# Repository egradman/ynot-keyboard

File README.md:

# zmq-corne6

This is the repo for my "ynot" keyboard.

it uses:

- Panasonic EVQWGD001 (purchased from keebd, but you can find them on aliexpress)
- nicenano
- a r61 trackpoint harvested from this keyboard https://www.ebay.com/itm/255174965511.  see https://deskthority.net/wiki/TrackPoint_Hardware for the pinout.
- choc kailh whites
- custom laser cut case
- battery:  3.7v 110mAh 301230 see (https://typeractive.xyz/products/lithium-battery-110mah)

trackpoint reset circuit as described here https://github.com/alonswartz/trackpoint

and the firmware provided by infusedkim https://github.com/infused-kim/kb_zmk_ps2_mouse_trackpoint_driver

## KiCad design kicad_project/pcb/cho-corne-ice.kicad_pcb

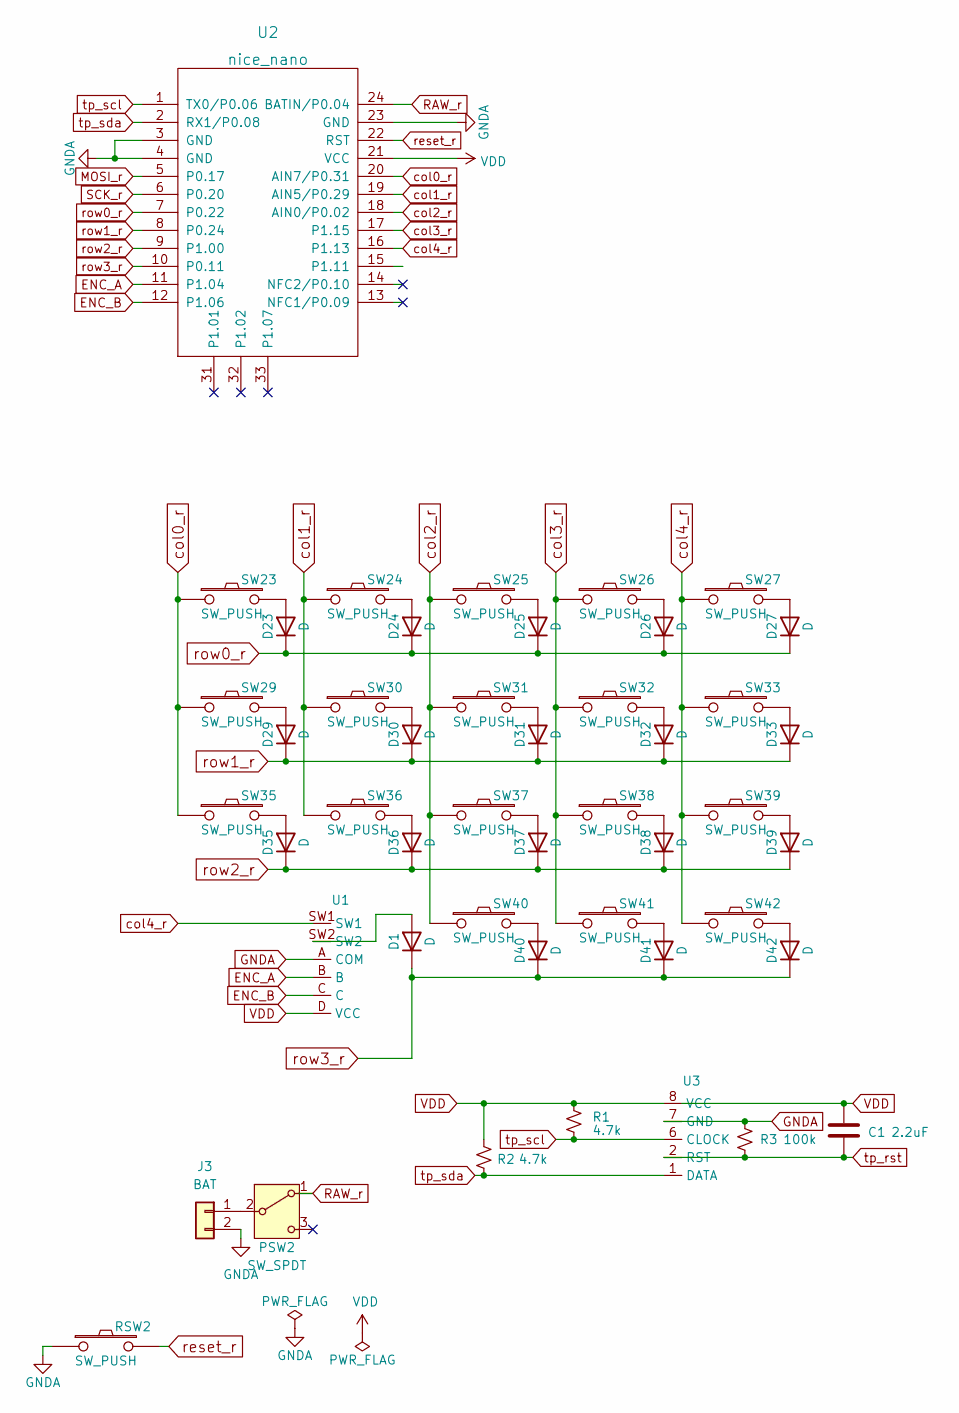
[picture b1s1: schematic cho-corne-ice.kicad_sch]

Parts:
C1: 2.2uF; CP_Radial_D4.0mm_P1.50mm
D1, D23, D24, D25, D26, D27, D29, D30, D31, D32, D33, D35, D36, D37, D38, D39, D40, D41, D42: D; ComboDiode
J3: BAT; SolderWire-0.1sqmm_1x02_P3.6mm_D0.4mm_OD1mm
PSW2: SW_SPDT; power_switch
R1, R2: 4.7k; R_Axial_DIN0204_L3.6mm_D1.6mm_P5.08mm_Horizontal
R3: 100k; R_Axial_DIN0204_L3.6mm_D1.6mm_P5.08mm_Horizontal
RSW2: SW_PUSH; reset_switch
SW23, SW24, SW25, SW26, SW27, SW29, SW30, SW31, SW32, SW33, SW35, SW36, SW37, SW38, SW39, SW40, SW41, SW42: SW_PUSH; SW_PG1350_reversible
U1: RollerEncoder_Panasonic_EVQWGD001
U2: nice_nano; ProMicro_jumpable_eric
U3: trackpoint

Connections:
ENC_A: U1.B, U2.11 (P1.04)
ENC_B: U1.C, U2.12 (P1.06)
GNDA: J3.2, R3.1, RSW2.1, U1.A (COM), U2.3 (GND), U2.4 (GND), U2.23 (GND), U3.7 (GND)
MOSI_r: U2.5 (P0.17)
unnamed: D1.2 (A), U1.SW2
unnamed: D23.2 (A), SW23.2
unnamed: D24.2 (A), SW24.2
unnamed: D25.2 (A), SW25.2
unnamed: D26.2 (A), SW26.2
unnamed: D27.2 (A), SW27.2
unnamed: D29.2 (A), SW29.2
unnamed: D30.2 (A), SW30.2
unnamed: D31.2 (A), SW31.2
unnamed: D32.2 (A), SW32.2
unnamed: D33.2 (A), SW33.2
unnamed: D35.2 (A), SW35.2
unnamed: D36.2 (A), SW36.2
unnamed: D37.2 (A), SW37.2
unnamed: D38.2 (A), SW38.2
unnamed: D39.2 (A), SW39.2
unnamed: D40.2 (A), SW40.2
unnamed: D41.2 (A), SW41.2
unnamed: D42.2 (A), SW42.2
unnamed: J3.1, PSW2.2 (B)
RAW_r: PSW2.1 (A), U2.24 (BATIN/P0.04)
SCK_r: U2.6 (P0.20)
VDD: C1.1, R1.1, R2.1, U1.D (VCC), U2.21 (VCC), U3.8 (VCC)
col0_r: SW23.1, SW29.1, SW35.1, U2.20 (AIN7/P0.31)
col2_r: SW25.1, SW31.1, SW37.1, SW40.1, U2.18 (AIN0/P0.02)
col3_r: SW26.1, SW32.1, SW38.1, SW41.1, U2.17 (P1.15)
reset_r: RSW2.2, U2.22 (RST)
row0_r: D23.1 (K), D24.1 (K), D25.1 (K), D26.1 (K), D27.1 (K), U2.7 (P0.22)
row1_r: D29.1 (K), D30.1 (K), D31.1 (K), D32.1 (K), D33.1 (K), U2.8 (P0.24)
row2_r: D35.1 (K), D36.1 (K), D37.1 (K), D38.1 (K), D39.1 (K), U2.9 (P1.00)
row3_r: D1.1 (K), D40.1 (K), D41.1 (K), D42.1 (K), U2.10 (P0.11)
tp_rst: C1.2, R3.2, U3.2 (RST)
tp_scl: R1.2, U2.1 (TX0/P0.06), U3.6 (CLOCK)
tp_sda: R2.2, U2.2 (RX1/P0.08), U3.1 (DATA)

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
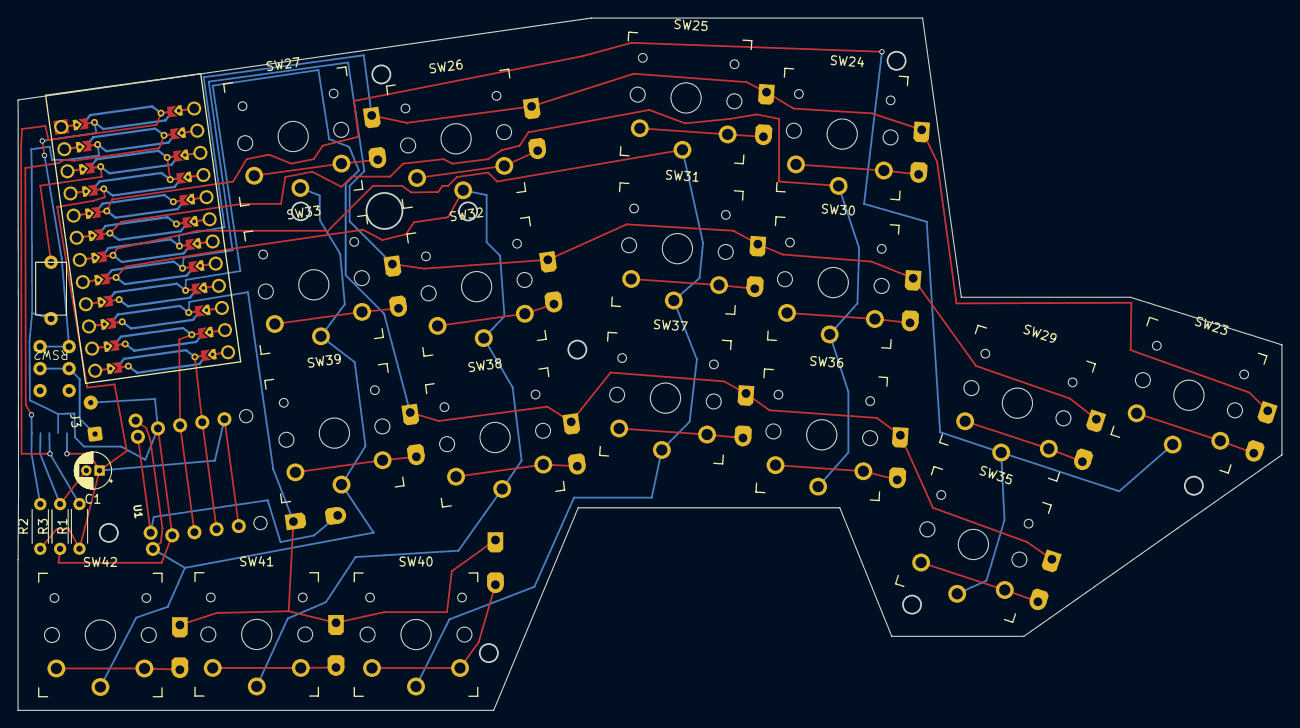
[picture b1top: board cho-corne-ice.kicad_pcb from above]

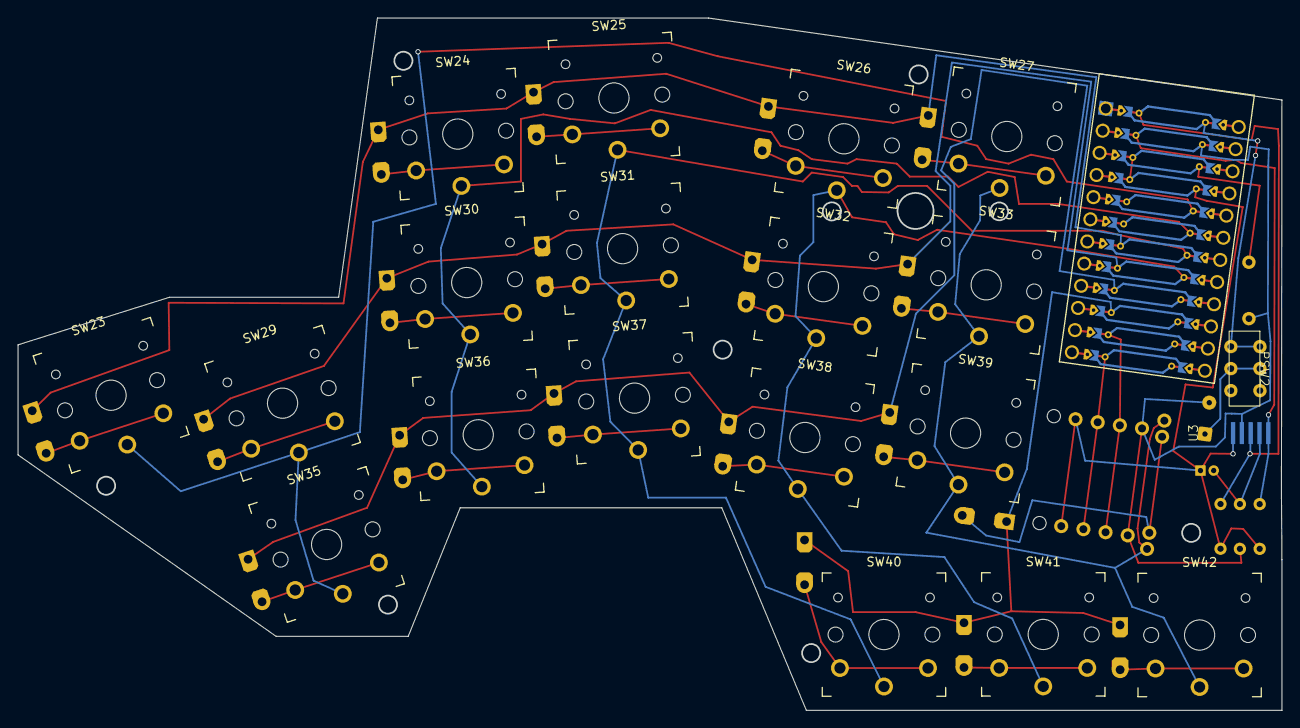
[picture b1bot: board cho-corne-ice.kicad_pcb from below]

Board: 2 copper layers, 143.4 x 78.5 mm, 47 parts (20 on the bottom side), 38 nets.

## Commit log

2024-10-14 invert y
2024-10-14 name
2024-10-14 more logging
2024-10-14 update layers
2024-10-14 updated pins
2024-10-14 restore pins
2024-10-14 pins
2024-10-14 les logging
2024-10-14 uart logging
2024-10-14 build use correct shield
2024-10-14 rename some configs
2024-10-14 correct keys
2024-10-14 change lag activation
2024-10-14 scroll
2024-10-14 scroll and buttons
2024-10-15 remove auto tp layer
2024-10-15 combo clicks
2024-10-15 fix syntax error
2024-10-15 middle click
2024-11-05 updated shift and moved control b
2024-11-05 fixed control b
2024-11-17 updating keymap for 36 keys only
2024-11-17 changing off by one
2024-11-17 update off by one
2024-11-17 update combos
2024-11-17 attempt at encoder bindings
2024-11-17 arrows
2024-11-18 another attempt at scroll
2024-11-18 amend
2024-11-18 add tap-ms
2024-11-18 increase tap-ms on scroll
2024-11-20 added kicad
2024-11-20 readme
2024-11-21 testing some new values for scrolling
2024-11-21 more scroll stuff
2024-11-21 try again with pete feature branch
2024-11-21 whoops wrong repo
2024-11-21 something wrong with usb logging
2024-11-22 more usb symbols
2024-11-22 trying again with original repo
2024-11-22 little tuning, looking good with orig repo
2024-11-22 more tuning
2024-11-22 speed up the trackpoint
2024-11-22 now for real
2024-12-19 trying new less than greater than
2024-12-19 new control b
2025-02-05 revert trackpoint modification
2025-02-09 changing caps_word
2025-02-09 syntax error
2025-02-09 syntax error2
2025-02-09 added real sk shift
2025-02-14 better caps lock
2025-02-15 speed up combo timeout
2025-02-15 speed up even more
2025-02-23 cleanup
2025-02-23 unspeed combos
2025-02-23 unknown syntax error
2025-02-23 moving more stuff around because I hate being productive
2025-02-23 syntax
2025-02-24 change tab binding
2025-02-24 general syntax and cleanup
2025-03-05 debounce
2025-03-05 tp sensitivity
2025-03-05 more debounce
